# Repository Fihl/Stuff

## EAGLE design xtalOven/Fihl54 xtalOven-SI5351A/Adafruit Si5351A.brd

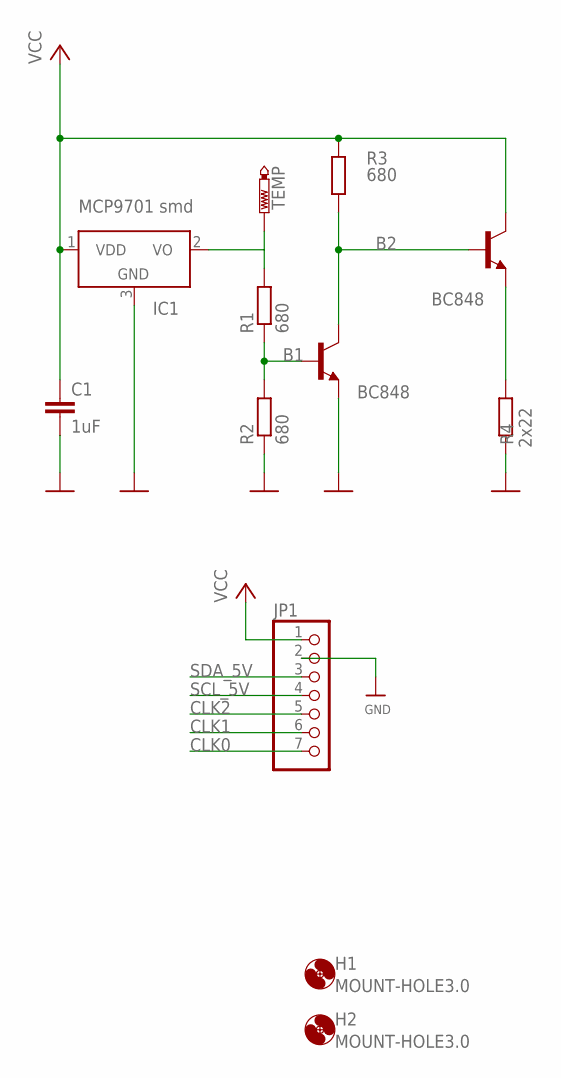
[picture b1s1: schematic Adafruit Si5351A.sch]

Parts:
C1: 1uF; C1210
H1, H2: MOUNT-HOLE3.0; 3,0
IC1: MCP9701 smd; SOT23-3
JP1: HEADER-1X7THICKER; 1X07_ROUND_76
R1, R2, R3: 680; M1206
R4: 2x22; M1206
T1, T2: BC848; SOT23
TEMP: PTR1TP10SQ; TP10SQ

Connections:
B1: R1.1, R2.2, T1.1 (B)
B2: R3.1, T1.3 (C), T2.1 (B)
CLK0: JP1.7
CLK1: JP1.6
CLK2: JP1.5
E2: R4.2, T2.2 (E)
GND: C1.2, IC1.3 (GND), JP1.2, R2.1, R4.1, T1.2 (E)
SCL_5V: JP1.4
SDA_5V: JP1.3
TEMP: IC1.2 (VO), R1.2, TEMP.TP
VCC: C1.1, IC1.1 (VDD), JP1.1, R3.2, T2.3 (C)

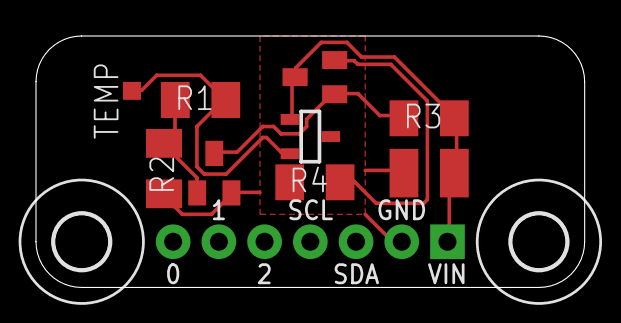
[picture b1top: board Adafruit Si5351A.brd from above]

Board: 2 copper layers, 30.5 x 14.0 mm, 12 parts (0 on the bottom side), 6 nets.

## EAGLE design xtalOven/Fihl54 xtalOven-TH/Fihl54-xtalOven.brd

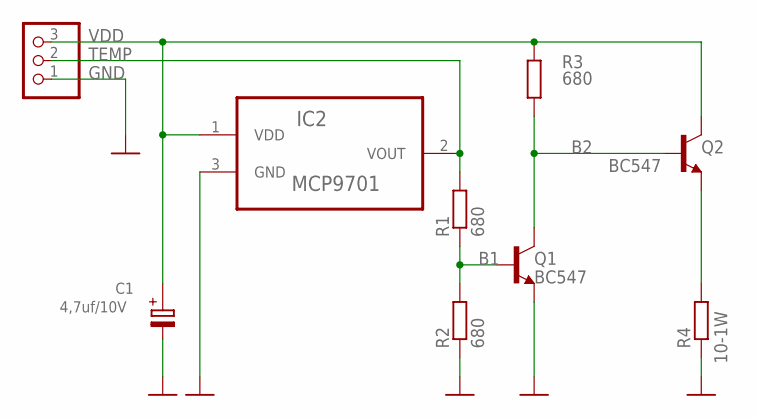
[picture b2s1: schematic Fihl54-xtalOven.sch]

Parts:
C1: 4,7uf/10V; E2,5-5
IC2: MCP9701; TO127P254X533-3
JP1: jp1; 1X03
Q1, Q2: BC547; TO92
R1, R2, R3: 680; 0309V
R4: 10-1W; 0309V

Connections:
B1: Q1.2 (B), R1.1, R2.2
B2: Q1.3 (C), Q2.2 (B), R3.1
E2: Q2.1 (E), R4.2
GND: C1.-, IC2.3 (GND), JP1.1, Q1.1 (E), R2.1, R4.1
TEMP: IC2.2 (VOUT), JP1.2, R1.2
VDD: C1.+, IC2.1 (VDD), JP1.3, Q2.3 (C), R3.2

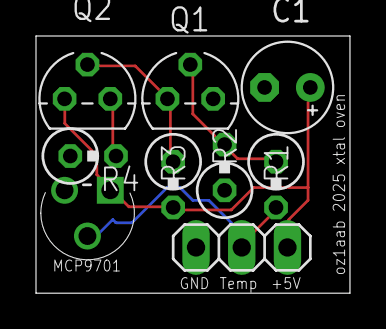
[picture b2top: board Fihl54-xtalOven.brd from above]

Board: 2 copper layers, 17.4 x 14.3 mm, 9 parts (0 on the bottom side), 6 nets.

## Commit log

2024-07-20 Demo af MQTT, SSL, DHT22, DeepSleep
2024-07-27 ESP-IDF in VSCode, deep-sleep
2024-07-29 More RTC turn off
2024-10-11 Public on FB
2024-10-12 Added CPU ESP32-C3 reference
2024-10-13 saved
2024-10-20 ArduinoDueKeyerUSB
2024-10-20 Laser box scripts i scad filen
2025-07-31 xtal
2025-07-31 xtal oven

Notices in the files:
parts and their libraries:
microbuilder: This work is placed in the public domain, and may be freely used for commercial and non-commercial work with the following conditions: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
